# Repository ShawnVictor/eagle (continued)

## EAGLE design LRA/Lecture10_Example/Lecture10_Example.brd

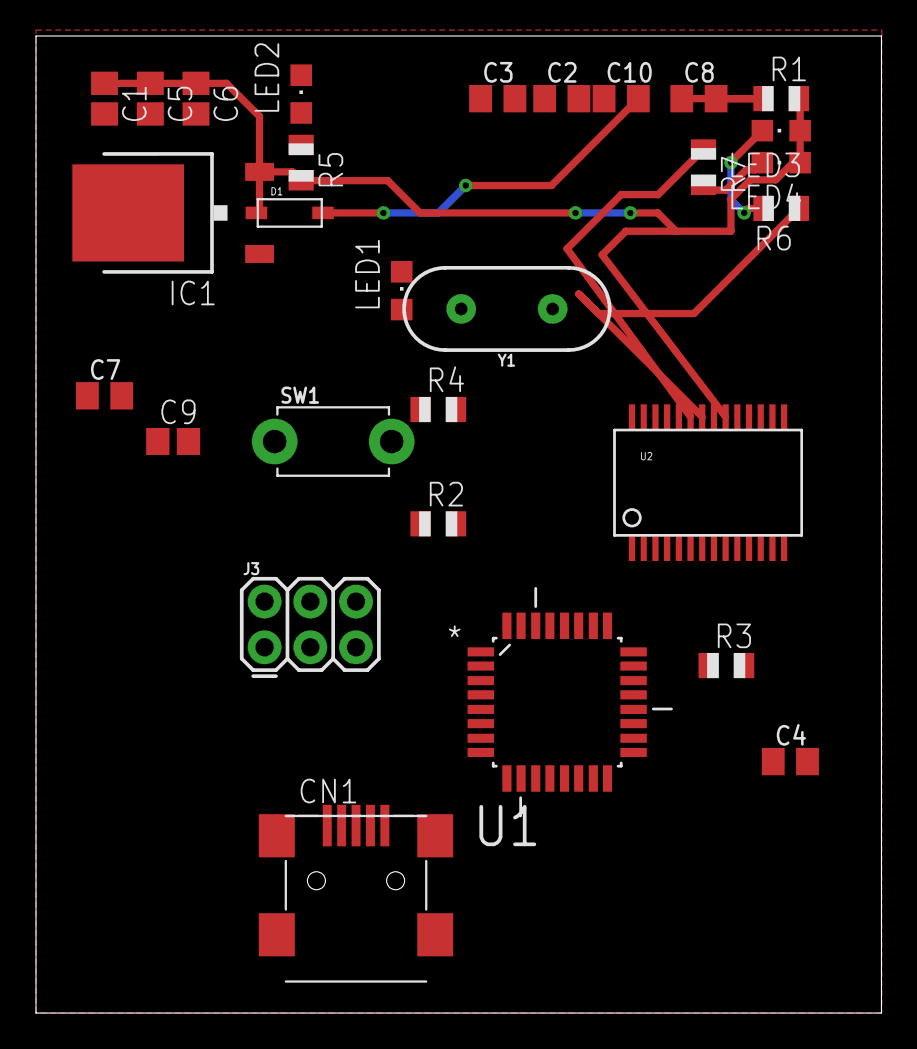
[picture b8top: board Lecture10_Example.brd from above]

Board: 2 copper layers, 47.0 x 54.3 mm, 29 parts (0 on the bottom side), 25 nets.

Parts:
C1: 0.1uF; C0805
C2, C3: 15pF; 0805
C4, C7, C8, C10: 0.1uF; 0805
C5, C6, C9: 4.7uF; C0805
CN1: USB-MINIB
D1: SOD-123
IC1: 7824DT; TO252
J3: FEMALE 2x3; 2X3
LED1, LED2, LED3, LED4: CHIPLED_0805
R1, R4, R5, R6, R7: 680; R0805
R2, R3: 100; R0805
SW1: TACT_PANA-EVQ
U1: ATMEGA328P-AU; QFP80P900X900X120-32N
U2: SSOP28DB
Y1: 16MHz; HC49US

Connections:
3.3V: C7.2, U2.17
+5V: C1.1, C5.1, C6.1, D1.C, IC1.2, LED3.A, LED4.A, R1.2, R5.2, U1.4, U1.6, U1.18, U2.4, U2.20
AREF: C4.1, U1.20
D0/RX: R2.1, U2.1
D1/TX: R3.1, U2.5
D11/MOSI: J3.4, U1.15
D12/MISO: J3.1, U1.16
D13/SCK: J3.3, R4.2, U1.17
GND: C1.2, C2.1, C3.1, C4.2, C5.2, C6.2, C7.1, C9.2, C10.1, CN1.GND, IC1.3, J3.6, LED1.C, LED2.C, SW1.P$2, U1.3, U1.5, U1.21, U2.7, U2.18, U2.21, U2.25
unnamed: C3.2, U1.8, Y1.2
unnamed: C2.2, U1.7, Y1.1
unnamed: LED2.A, R5.1
unnamed: CN1.D+, U2.15
unnamed: CN1.D-, U2.16
unnamed: R2.2, U1.30
unnamed: R3.2, U1.31
unnamed: LED3.C, R6.2
unnamed: LED1.A, R4.1
unnamed: R6.1, U2.22
unnamed: R7.1, U2.23
unnamed: C8.1, U2.2
unnamed: LED4.C, R7.2
RESET: C8.2, J3.5, R1.1, SW1.P$1, U1.29
VIN: IC1.1, J3.2
VUSB: C9.1, C10.2, CN1.VBUS, D1.A
